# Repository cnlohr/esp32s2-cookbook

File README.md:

# esp32s2-cookbook
Low-level tests with the ESP32-S2

TODO: 
 * Check out RTCIO_SAR_I2C_IO_REG -> Does it reveal anything?

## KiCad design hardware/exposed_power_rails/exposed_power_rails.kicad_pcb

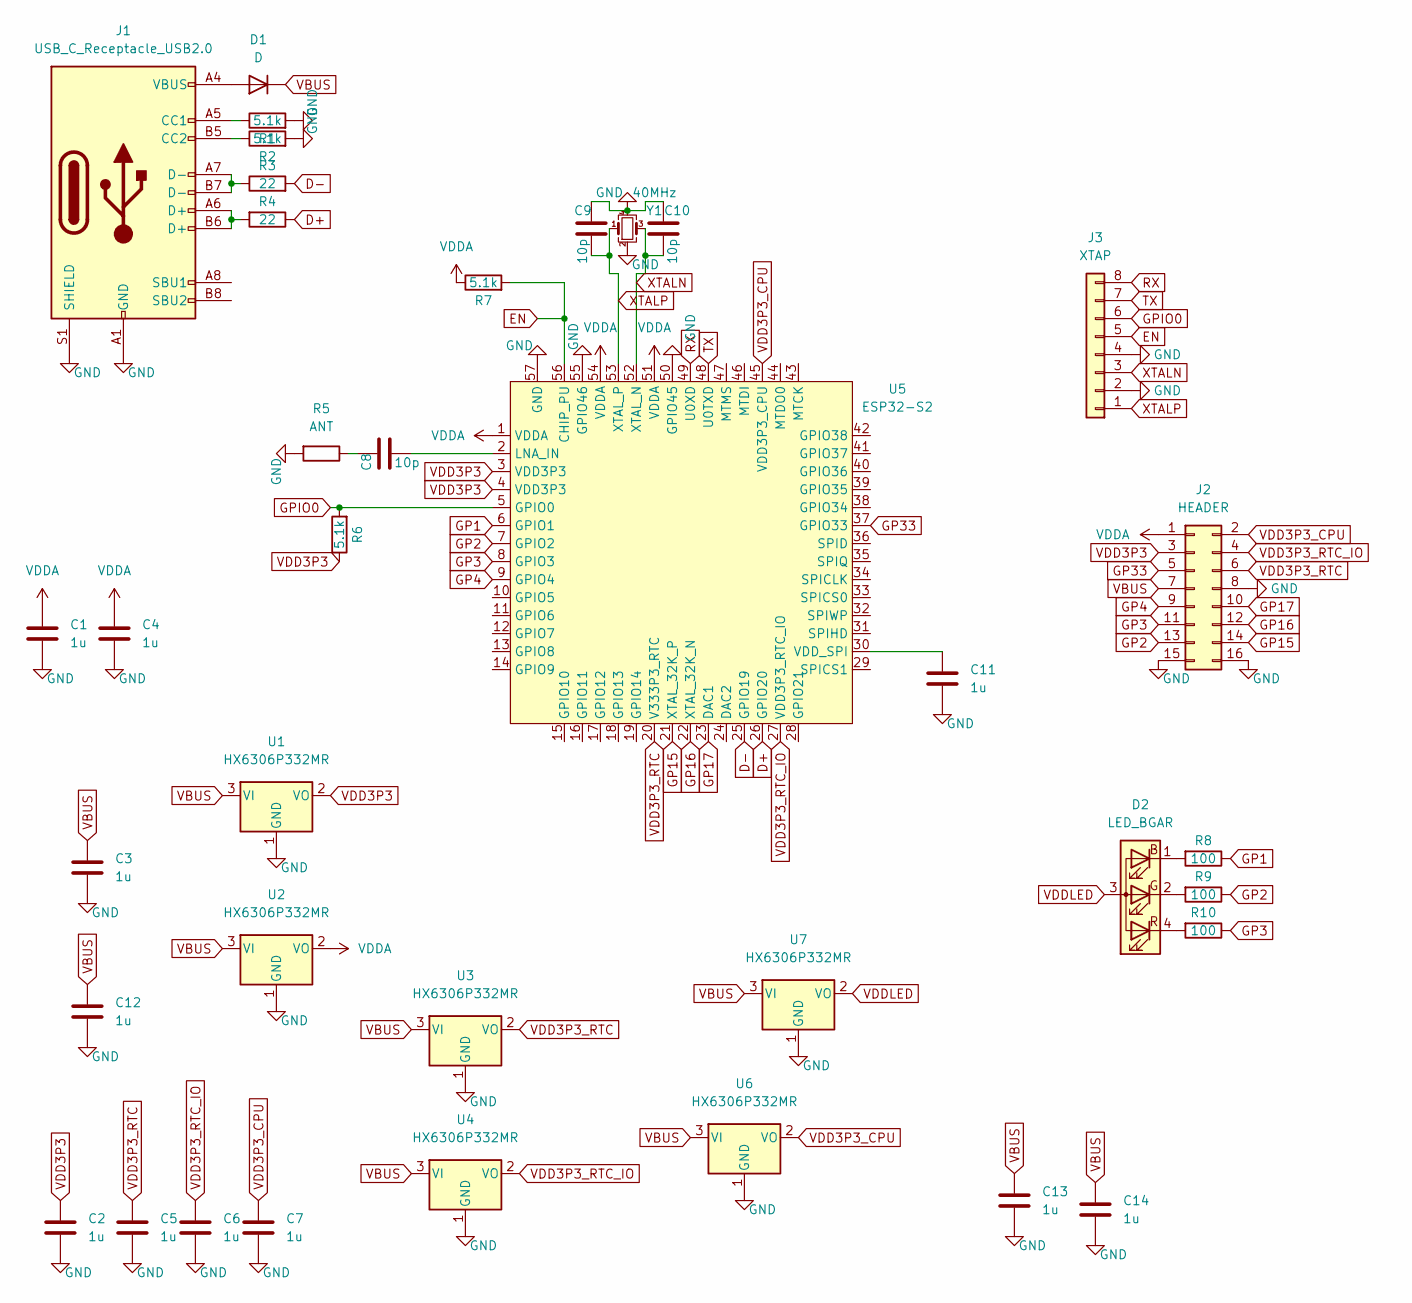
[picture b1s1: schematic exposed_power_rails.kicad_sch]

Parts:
C1, C2, C3, C4, C5, C6, C7, C11, C12, C13, C14: 1u; C_0201_0603Metric; LCSC C295898
C8, C9, C10: 10p; C_0201_0603Metric; LCSC C161369
D1: D; D_SOD-123F; LCSC C426570
D2: LED_BGAR; LED_Cree-PLCC4_2x2mm_CW; LCSC C2874116
J1: USB_C_Receptacle_USB2.0; USB_C_Receptacle_HRO_TYPE-C-31-M-12; LCSC C2765186
J2: HEADER; PinHeader_2x08_P2.54mm_Vertical; LCSC C492425
J3: XTAP; PinHeader_1x08_P2.54mm_Vertical; LCSC C2894931
R1, R2, R6, R7: 5.1k; R_0201_0603Metric; LCSC C473460
R3, R4: 22; R_0201_0603Metric; LCSC C144010
R5: ANT; Texas_SWRA117D_2.4GHz_Left
R8, R9, R10: 100; R_0201_0603Metric; LCSC C77623
U1, U2, U3, U4, U6, U7: HX6306P332MR; SOT-23; LCSC C296211
U5: ESP32-S2; ESP32S2; LCSC C2840995
Y1: 40MHz; Crystal_SMD_2016-4Pin_2.0x1.6mm; LCSC C648970

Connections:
D+: R4.1, U5.26 (GPIO20)
D-: R3.2, U5.25 (GPIO19)
EN: J3.5, R7.2, U5.56 (CHIP_PU)
GND: C1.2, C2.2, C3.2, C4.2, C5.2, C6.2, C7.2, C9.1, C10.1, C11.2, C12.2, C13.2, C14.2, J1.A1 (GND), J1.A12 (GND), J1.B1 (GND), J1.B12 (GND), J1.S1 (SHIELD), J2.8, J2.15, J2.16, J3.2, J3.4, R1.2, R2.2, R5.2, U1.1 (GND), U2.1 (GND), U3.1 (GND), U4.1 (GND), U5.50 (GPIO45), U5.55 (GPIO46), U5.57 (GND), U6.1 (GND), U7.1 (GND), Y1.2, Y1.4
GP1: R8.1, U5.6 (GPIO1)
GP2: J2.13, R9.1, U5.7 (GPIO2)
GP3: J2.11, R10.1, U5.8 (GPIO3)
GP4: J2.9, U5.9 (GPIO4)
GP15: J2.14, U5.21 (XTAL_32K_P)
GP16: J2.12, U5.22 (XTAL_32K_N)
GP17: J2.10, U5.23 (DAC1)
GP33: J2.5, U5.37 (GPIO33)
GPIO0: J3.6, R6.2, U5.5 (GPIO0)
unnamed: C8.1, R5.1
unnamed: C8.2, U5.2 (LNA_IN)
unnamed: C11.1, U5.30 (VDD_SPI)
unnamed: D1.2 (A), J1.A4 (VBUS), J1.A9 (VBUS), J1.B4 (VBUS), J1.B9 (VBUS)
unnamed: D2.1 (BK), R8.2
unnamed: D2.2 (GK), R9.2
unnamed: D2.4 (RK), R10.2
unnamed: J1.A5 (CC1), R1.1
unnamed: J1.A6 (D+), J1.B6 (D+), R4.2
unnamed: J1.A7 (D-), J1.B7 (D-), R3.1
unnamed: J1.B5 (CC2), R2.1
RX: J3.8, U5.49 (U0XD)
TX: J3.7, U5.48 (U0TXD)
VBUS: C3.1, C12.1, C13.1, C14.1, D1.1 (K), J2.7, U1.3 (VI), U2.3 (VI), U3.3 (VI), U4.3 (VI), U6.3 (VI), U7.3 (VI)
VDD3P3: C2.1, J2.3, R6.1, U1.2 (VO), U5.3 (VDD3P3), U5.4 (VDD3P3)
VDD3P3_CPU: C7.1, J2.2, U5.45 (VDD3P3_CPU), U6.2 (VO)
VDD3P3_RTC: C5.1, J2.6, U3.2 (VO), U5.20 (V333P3_RTC)
VDD3P3_RTC_IO: C6.1, J2.4, U4.2 (VO), U5.27 (VDD3P3_RTC_IO)
VDDA: C1.1, C4.1, J2.1, R7.1, U2.2 (VO), U5.1 (VDDA), U5.51 (VDDA), U5.54 (VDDA)
VDDLED: D2.3 (A), U7.2 (VO)
XTALN: C10.2, J3.3, U5.52 (XTAL_N), Y1.3
XTALP: C9.2, J3.1, U5.53 (XTAL_P), Y1.1

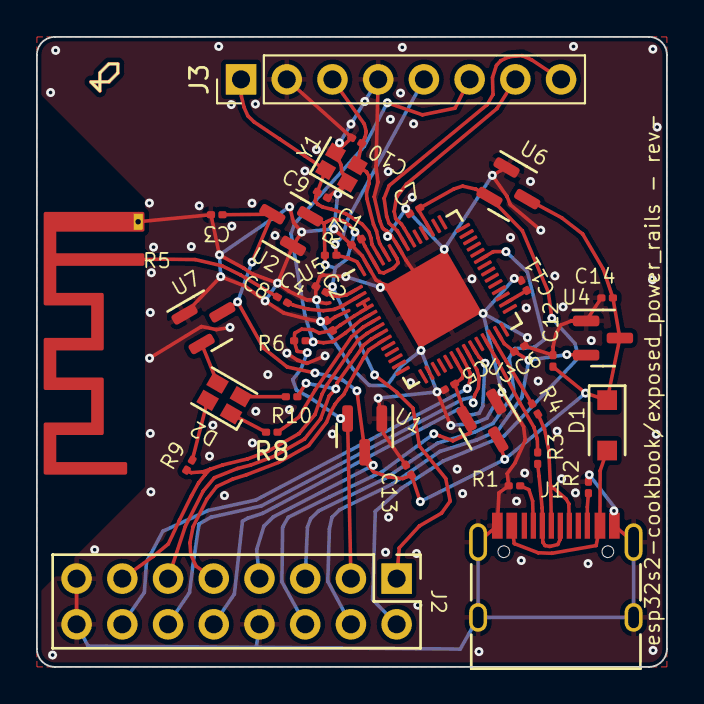
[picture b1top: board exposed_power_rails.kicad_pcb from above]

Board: 2 copper layers, 35.0 x 35.0 mm, 37 parts (0 on the bottom side), 35 nets.

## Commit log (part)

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2022-07-18 Add first cookbook thing.
2022-07-19 Update with a SAR ADC DIG Example.
2022-07-19 Bump versions.
2022-07-19 Bump
2022-07-19 Significantly improve documentation.
2022-07-20 Rename sandbox-with-idf-rmt.c to sandbox-with-idf-rmt_using_idf.c
2022-07-21 Rename sandbox_fake_touch_with_rmt_module.c to sandbox_fake_touch_with_rmt_module_no_idf.c
2022-08-21 Add runfromram, and tweak overclock example
2022-08-21 Almost working.
2022-08-21 Transitioning over to cpq's stuff.
2022-08-22 Getting close.
2022-08-22 FLASH WORKING
2022-08-22 Reliable overclocking measurements.
2022-08-22 bump with script note
2022-08-22 More cleanup
2022-08-29 Use fast PLL
2022-09-03 moving name
2022-09-04 Add RGB LED
2022-09-04 Update examples
2022-09-04 Fix bug in RGB Hue vals
2022-09-04 cleanup
2023-01-21 Add initial sandbox flashing tool.
2023-01-21 Rename and update dev sandbox work.
2023-01-21 Add existing sandboxes from swadges.
2023-01-21 Update everything to work with the ULP as well.
2023-01-21 Add FSM exmaple. Hint: It's not faster than the RISC-V :(
2023-01-23 Add hardware.
2023-01-23 Switch name of sandbox folder.
2023-01-23 Update sandbox
2023-01-29 Update USB control code.
2023-03-01 Add example for using pro alone GPIO
2023-03-01 Add demo with ch32v003_swio.
2023-03-01 Update! Able to reliably communicate with the CH32V003!
2023-03-01 Further optimizations.
2023-03-01 Rename swio interface check tool
2023-03-01 Update notes in file.
2023-03-01 Add notes.
2023-03-02 Add glitch mode, where you don't even need a pullup.
2023-03-02 Able to enter/exit halt mode.
2023-03-04 Tweaks to the swio protocol work.
2023-03-05 Add CH32V003 Programmer.
2023-03-05 Add updates
2023-03-05 Update - working programmer.
2023-03-05 Update readme/testapp
2023-03-05 Remove tusb BSP
2023-03-12 Interim work - incomplete, but it does work.
2023-03-12 Update! Working with block write.
2023-03-12 working unbrick
2023-03-12 Be smart about re-trying reads.
2023-03-13 Update programmer
2023-03-13 Minimal I2S test.
2023-03-13 Remove unused parts of libusb. + add needed build system features.
2023-03-13 added signal generator functionality
2023-03-14 Need to pull-down power.
2023-03-15 Add native printf support.
2023-03-29 Fix IOs for output
2023-03-29 Update note about output pins
2023-04-21 Fix comment.
2023-04-23 add pin definitions
    fixed pin naming
    fix teardown pwr seq
    schem - png to jpg
    remove schematic
2023-05-01 Clarify comment for autoinc
2023-05-04 prevent corruption of overwrittenf rames from taking for forever
2023-05-08 Update with note about how to just flash.
2023-05-24 Add additional call to pull USB Data lines low during reboot into bootloader to ensure host reeunmerates USB
2023-06-05 Indicate IDF version v5.0 needed to build CH32V003 programmer.
2023-06-09 Remove unneeded wait + improve error reporting when encountering flash errors.
2023-06-13 Fix SWIO pin error in readme
    Unless I'm mistaken, the pin for SWIO is PD1 according to this datasheet http://www.wch-ic.com/downloads/CH32V003DS0_PDF.html
2023-06-23 fixed pin definitions and default board
2023-06-27 Add some basic support for the new ronboe.
2023-06-27 Oops - invert colors
2023-06-27 Add dedicated firmware for screen writing
2023-06-27 Cleanup and allow full row-set writing at once.
2023-06-30 Fix up per-line-graph
2023-06-30 Improve graphing
2023-07-31 add target power on delay
2023-08-01 Update to newest IDF.
2023-08-17 Update toolset a little
2024-01-31 * Make it work with the new 5.1 SDK * Add a rf transmitter test
2024-02-01 Add more code getting closer to a software build
2024-02-02 IT LIVE (and sends garbage)
2024-02-02 New local minima
2024-02-02 More of our messages are getting through (though it's still not being decoded correctly)
2024-02-03 Update with gnuradio blocks
2024-02-03 Add rtlsdr rules
2024-02-03 Found a concoction of data which triggers a lot of poignent chunks being received on a mikrotik.
2024-02-03 Dang we're getting close.
2024-02-03 Use new style of transport to minimize impact
2024-02-04 General updates - this seems to get a lot of packets through.
    Time to see if I can push in the direction/values.
2024-02-04 Switch to pre-computing everything.
2024-02-04 Every packet I send seems to be decoded by the Mikrotik
2024-02-04 SOME PACKETS ARE PASSING without CRC errors.
2024-02-04 Working toward SF9
2024-02-05 SF11 almost working
2024-02-05 Stake in the sand for SF11
2024-02-05 Is this a crash?
2024-02-05 Not working
2024-02-05 Fixed - working as it was before.
2024-02-05 Pretty solid working - need to move back to laptop for SF11 and SF6
2024-02-05 Just tweaking some things.
2024-02-05 Stabler by adding an offset
2024-02-05 Examine error patterns.
2024-02-05 Cleaned up a little more
2024-02-09 Update toolbox
2024-02-11 Add comment about upstream
2024-02-12 Update to new version of the LoRa SDR Code
2024-02-12 Checkin for SF7-SF10
2024-02-12 Oops - real checking for SF7-10
2024-02-12 Another checkin for SF7-10
2024-03-25 * Make it work with the new 5.1 SDK
2024-05-09 Mention other S2 versions and issues with serial USB converters.
2024-05-29 Add first shot at UPDI programming. Getting there slowly.
2024-05-29 Bleh few more tweaks - giving up
2024-05-29 Try without erase
2024-05-30 Working UPDI Programmer
2024-05-30 Update!
2024-05-30 Add movement note
2024-05-30 Add UPDI programming
2024-05-30 Precompute updi in example
2024-10-06 Fix build for regular programming.
2024-11-06 Trying to do RVSWD, it's not going great.
2024-11-08 Getting very close to a functioning RVSWD
2024-11-09 Continuing work
2024-11-09 Still not quite working, middle of debugging
2024-11-09 Working on x035
2024-11-10 Working with everythg but v30x it seems?
2024-11-10 Working SWIO interface
2024-11-10 Add RVSWD support
2025-01-10 Bump with images
2025-02-08 Tweak some values
2025-02-09 Bump to working board set, fixing printf
2025-02-09 Add 006 programmer
2025-02-18 don't uprintf() while interrupts disabled
    This was causing a crash when aliased to printf() due to failing to block and acquire a lock inside newlib while interrupts were disabled
2025-03-01 Fixup for ch32v00x
2025-03-01 Tidy up and fixup, this definitely works well now
2025-03-02 tud_hid_gamepad_report causes problems in Windows. This disables that.
2025-03-04 * Bump version number * Allow host to override chip configuration
2025-03-04 Add timeout for waitfordoneop. Fix Read Data32 minimum read. Fix bug in ch32v20x/v30x writing
2025-03-04 Fix formatting for a (*++)
2026-01-20 Add ch5xx support
2026-01-20 Fix return on fail in MCFReadReg32
2026-01-29 Fix ch592. Update binaries
